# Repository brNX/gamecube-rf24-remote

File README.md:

# gamecube-rf24-remote

Remote control using an atmega88, nrf24l01+ and a Gamecube gamepad 

gamecube gamepad code adapted from [http://denki.world3.net/retro_v2.html](http://denki.world3.net/retro_v2.html)   
nrf24l01+ code adapted from  Maniacbug's rf24 library for arduino [https://github.com/maniacbug/RF24](https://github.com/maniacbug/RF24)

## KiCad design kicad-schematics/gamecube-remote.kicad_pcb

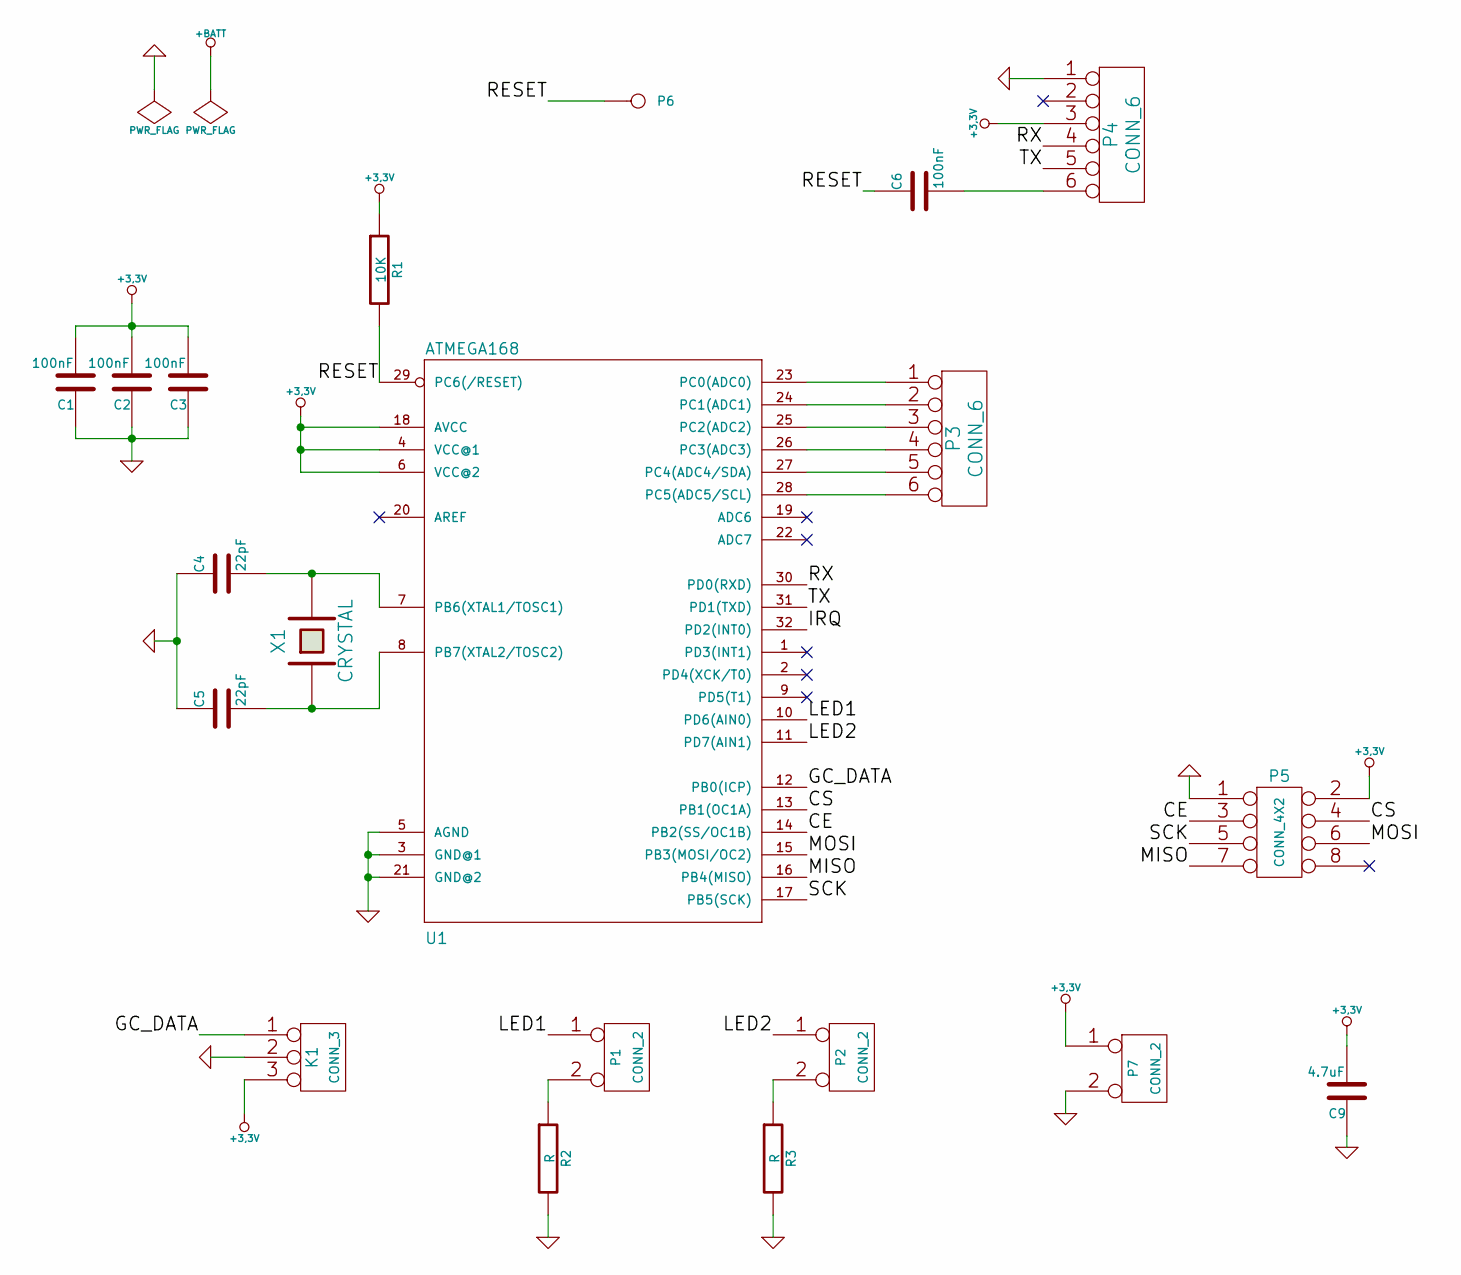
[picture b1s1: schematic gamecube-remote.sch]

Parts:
C1, C2, C3, C6: 100nF
C4, C5: 22pF
C9: 4.7uF
K1: CONN_3
P1, P2, P7: CONN_2
P3, P4: CONN_6
P5: CONN_4X2
P6: CONN_1
R1: 10K
R2, R3: R
U1: ATMEGA168; SparkFun-TQFP32-08
X1: CRYSTAL

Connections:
+3.3V: C1.2, C2.2, C3.2, C9.2, K1.3, P4.3, P5.2, P7.1, R1.1, U1.4 (VCC@1), U1.6 (VCC@2), U1.18 (AVCC); also elsewhere on the board
/CE: P5.3, U1.14 (PB2(SS/OC1B))
/CS: P5.4, U1.13 (PB1(OC1A))
/GC_DATA: K1.1, U1.12 (PB0(ICP))
/IRQ: U1.32 (PD2(INT0))
/LED1: P1.1, U1.10 (PD6(AIN0))
/LED2: P2.1, U1.11 (PD7(AIN1))
/MISO: P5.7, U1.16 (PB4(MISO))
/MOSI: P5.6, U1.15 (PB3(MOSI/OC2))
/RESET: C6.1, P6.1, R1.2, U1.29 (PC6(/RESET))
/RX: P4.4, U1.30 (PD0(RXD))
/SCK: P5.5, U1.17 (PB5(SCK))
/TX: P4.5, U1.31 (PD1(TXD))
GND: C1.1, C2.1, C3.1, C4.1, C5.1, C9.1, K1.2 (PM), P4.1, P5.1, P7.2 (PM), R2.2, R3.2, U1.3 (GND@1), U1.5 (AGND), U1.21 (GND@2); also elsewhere on the board
unnamed: P3.4, U1.26 (PC3(ADC3))
unnamed: P3.1, U1.23 (PC0(ADC0))
unnamed: P3.2, U1.24 (PC1(ADC1))
unnamed: P3.3, U1.25 (PC2(ADC2))
unnamed: P3.5, U1.27 (PC4(ADC4/SDA))
unnamed: P3.6, U1.28 (PC5(ADC5/SCL))
unnamed: C6.2, P4.6
unnamed: C5.2, U1.8 (PB7(XTAL2/TOSC2)), X1.1
unnamed: C4.2, U1.7 (PB6(XTAL1/TOSC1)), X1.2
unnamed: P2.2 (PM), R3.1
unnamed: P1.2 (PM), R2.1

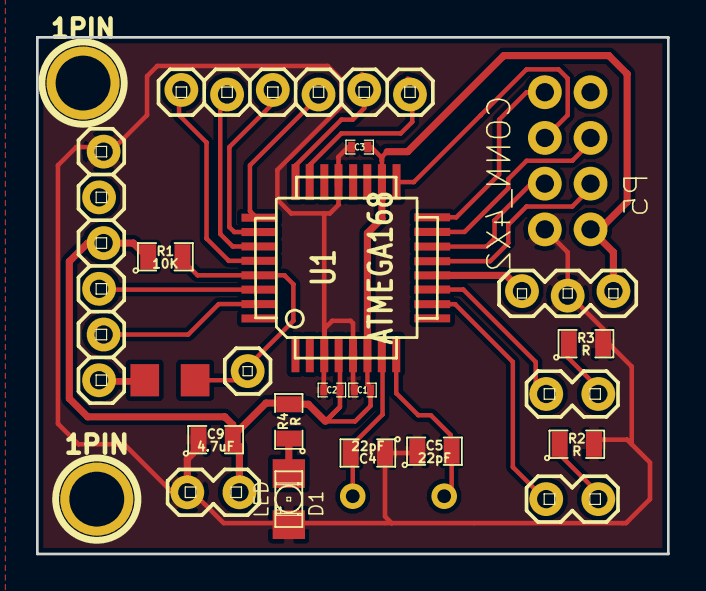
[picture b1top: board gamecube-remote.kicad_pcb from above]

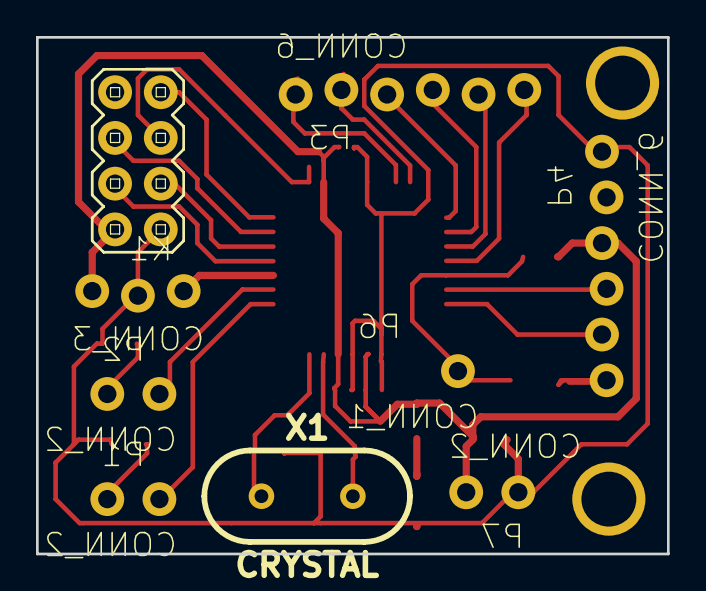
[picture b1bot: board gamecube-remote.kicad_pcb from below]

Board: 2 copper layers, 35.1 x 28.7 mm, 24 parts (2 on the bottom side), 25 nets.

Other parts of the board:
1PIN, 1PIN#2: P***; 1pin
D1: LED; LED-1206
R4: R; SM0805

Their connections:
+3.3V: R4.2; also elsewhere on the board
GND: D1.2; also elsewhere on the board
unnamed: D1.1, R4.1

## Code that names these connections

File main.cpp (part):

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
#include "rf24/RF24.h"

#define LED1 PB6
#define LED2 PB7

#define EEPROM_MAGIC_NUMBER 20

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	DDRD	= (1<<LED1) | (1<<LED2) ; //status led1 & 2 output
	PORTD	= 0;

	DDRB	&= ~(1<<PB0);
	PORTB	|=  (1<<PB0);	// PB0 input with pull-up

	sei();
}
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
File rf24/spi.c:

/*
 * spi.c
 *
 *  Created on: Apr 21, 2013
 *      Author: bgouveia
 */

#include "spi.h"

#define CS_PIN_PORT PORTB
#define CS_PIN PB1

#define CE_PIN_PORT PORTB
#define CE_PIN PB2

#define SCK PB5
#define MOSI PB3

  // When the SS pin is set as OUTPUT, it can be used as
  // a general purpose output port (it doesn't influence
  // SPI operations).
  //pinMode(SS, OUTPUT);


void spi_init(unsigned long bitrate,unsigned long datawidth){

	spi_cs_high();
	DDRB |=  (1<<PB2);


	// Enable SPI, Master, set clock rate fck/2 (maximum)
	SPCR = (1<<SPE)|(1<<MSTR);
	SPSR = (1<<SPI2X);

	DDRB 	|=  (1<<PB1) | (1<<SCK) | (1<<MOSI); // PB1(CE) ,  SCK and MOSI as output
}

void spi_cs_low()
{
	CS_PIN_PORT &= ~(1<<CS_PIN);
}

void spi_cs_high()
{
	CS_PIN_PORT |= (1<<CS_PIN);
}

void spi_ce_low()
{
	CE_PIN_PORT &= ~(1<<CE_PIN);
}

void spi_ce_high()
{
	CE_PIN_PORT |= (1<<CE_PIN);
}


uint8_t spi_transferByte(uint8_t _data){

	  SPDR = _data;
	  while (!(SPSR & _BV(SPIF)))
	    ;
	  return SPDR;
}

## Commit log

2013-05-05 timer2 for timeout, spi pins configuration
2013-05-05 spi working , rf24 working
2013-05-05 gamecube gamepad tested
2013-05-07 sleep
2013-06-02 calibration , everything tested
2013-06-02 README
2013-06-02 schematics
2013-06-02 refactor
2013-06-07 clamp values to min/max
2013-06-07 clamp function
2013-06-09 write and read calibration from eeprom
2013-06-16 reconnection bug fixed
2014-02-23 calibration variables and map from deadzone instead of 1
